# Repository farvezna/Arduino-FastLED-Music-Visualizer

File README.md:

# Arduino FastLED Music Visualizer
NOTE: I created my own PCB to hold an Arduino Nano to gain more practice with PCB layout and soldering through this cool project but all credits to code for RGB lighting are from Just Call Me Koko and the rest of the README below is of his works. The schematic used is essentially a replication of Sparkfun's spectrum shield mentioned below. My contributions are within the Nabid PCB folder.

<p align="center">
  
  <br>
  <a href="https://www.instagram.com/the.red.team4">Instagram</a>
 - <a href="https://www.youtube.com/channel/UCQdi3MDHHMm7u3cMkEY329Q">YouTube</a>
 - <a href="https://208.68.37.54">Website</a>
  <br>
  <br>
  <b>Like my content? Show your support by subscribing to my channel and following my page.</b>
</p>

# Table Of Constituents
- [Intro](#intro)
- [Setup](#setup)
  - [Video Tutorial](https://www.youtube.com/watch?v=Af74A0Tx-wA)
  - [Materials](#materials)
  - [Standalone Arduino UNO Setup](#standalone-arduino-uno-setup)
    - [Code](#code)
    - [Pins](#pins)
  - [Arduino UNO with Sparkfun Spectrum Shield Setup](#arduino-uno-with-sparkfun-spectrum-shield-setup)
    - [Code](#code)
    - [Pins](#pins)

## Intro
An Arduino based music visualizer using the FastLED library and a strip of individually addressable LEDs.  
Imagine this scenario. Does this not make you want to create your own music visualizer?

`> crawled inside of the neighbor's dog`  
`> dog walks inside of neighbor house`  
`> broke into neighbor house by being inside of dog`  
`> it is night now`  
`> brown cow`  
`> creep upstairs to find their mushroom farm`  
`> go into bed room`  
`> nothing`  
`> turn to leave`  
`> emergency yogurt falls out of pocket onto hardwood floor of bedroom`  
`> yogurt everywhere`  
`> wife gets up`  
`> slips on yogurt`  
`> impaled by mattress and is dead`  
`> yogurt murder`  
`> heinous Crims`  
`> power dump on dad's face so he doesn't feel as bad about his dead yogurt wife`  
`> poop yogurt and leave`  
`> poo and yogurt all over`  
`> in the air`  
`> zero gravity and poop`  

I can't find a guide worth a shit on YouTube or Github. I saw many videos showing a demo of a DIY music visualizer using these exact lights and an arduino. People seem to love to brag about how awesome their shit is but they won't show you how to make it. I have created this repo for anyone who faces the same challenge I did. I hope you find this useful and beneficial to your daily intake of fiber.

# Setup
So this is how to setup the most "dank" music visualizer ever.  
There will be two ways to set this puppy up. I prefer the second way, but that costs money.
There is a full video tutorial [here](https://www.youtube.com/watch?v=Af74A0Tx-wA)

## Materials
- [Arduino UNO](https://www.amazon.com/gp/product/B01N4LP86I/ref=oh_aui_detailpage_o06_s00?ie=UTF8&psc=1)
- [WS2812b Individually Addressable LEDs](https://www.amazon.com/gp/product/B01CDTEJBG/ref=oh_aui_detailpage_o09_s00?ie=UTF8&psc=1)
- [Sparkfun Spectrum Shield](https://www.amazon.com/gp/product/B00X0K30I6/ref=oh_aui_detailpage_o07_s00?ie=UTF8&psc=1) (second method)

## Standalone Arduino UNO Setup
### Code
  1. Open [this](https://github.com/the-red-team/Arduino-FastLED-Music-Visualizer/blob/master/music_visualizer.ino) code in your Arduino editor
  2. Line 13, adjust `NUM_LEDS` to the number of LEDs you plan to use
  3. Upload to your Arduino UNO
  
### Pins
  - 5v - Connect to Vcc on LED strip
  - GND - Connect to GND on LED strip
  - A0 - Connect to the other end of the 3.5mm jack connected to your music source
    - A0 must be pulled down with a resistor (shown in the picture below)
  - 6 - Connect to DATA on LED strip

## Arduino UNO with Sparkfun Spectrum Shield Setup
For this version of the music visualizer, you will need the [Sparkfun Spectrum Shield](https://www.amazon.com/gp/product/B00X0K30I6/ref=oh_aui_detailpage_o07_s00?ie=UTF8&psc=1)  
I prefer this version because it allows you to split the audio signal into 7 seperate channels (bass, mids, treb). This is important for anyone who wants their music visualizer to respond only to bass like mine.

### Code
  1. Open [this](https://github.com/the-red-team/Arduino-FastLED-Music-Visualizer/blob/master/music_visualizer_sparkfun_spectrum_shield.ino) code in your Arduino IDE
  2. Line 15, adjust `NUM_LEDS` to the number of LEDs you plan to use
  3. Install the FastLED library under "Manage Libraries"
  4. Upload to your Arduino UNO
  
### Pins
  - 5v - Connect to Vcc on LED strip
  - GND - Connect to GND on LED strip
  - 6 - Connect to DATA on LED strip

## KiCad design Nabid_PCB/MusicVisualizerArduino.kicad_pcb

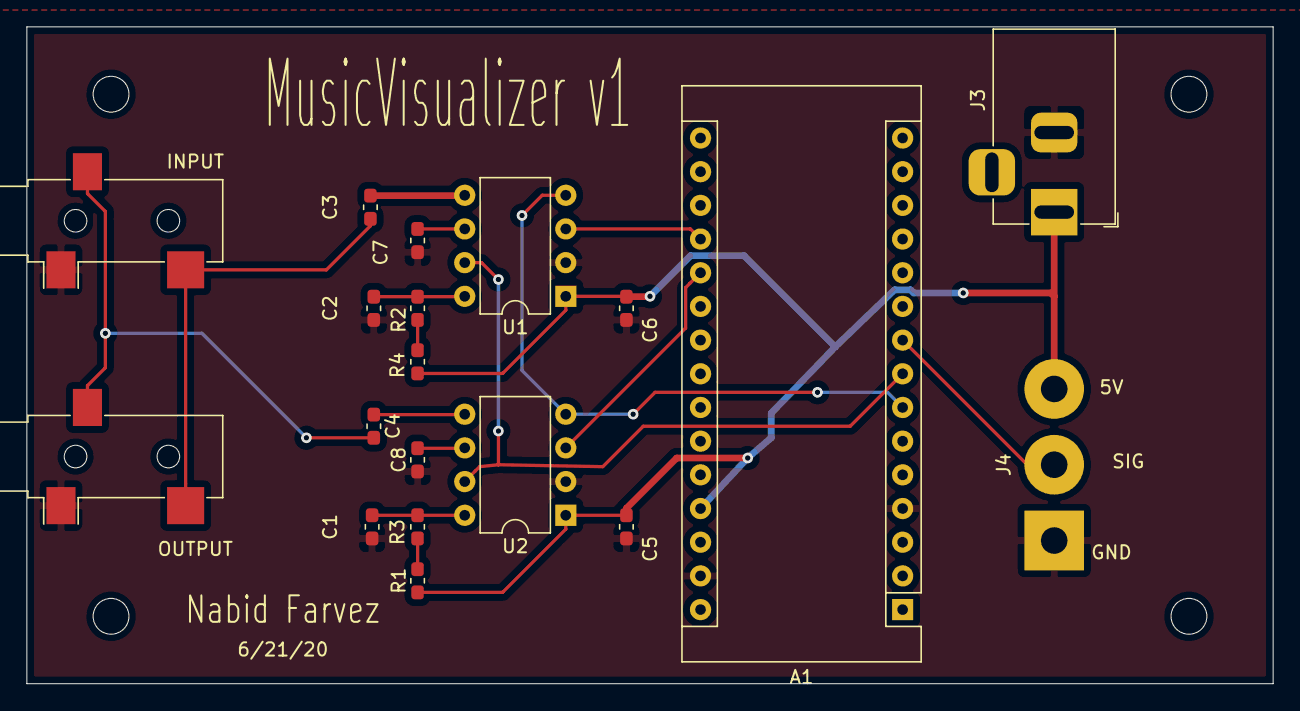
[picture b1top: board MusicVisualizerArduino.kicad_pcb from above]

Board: 2 copper layers, 94.0 x 49.5 mm, 19 parts (0 on the bottom side), 17 nets.

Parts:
A1: Arduino_Nano_v2.x; Arduino_Nano
C1, C2: 33 pF; C_0603_1608Metric_Pad1.05x0.95mm_HandSolder
C3, C4: 1 nF; C_0603_1608Metric_Pad1.05x0.95mm_HandSolder
C5, C6, C7, C8: 0.1 uF; C_0603_1608Metric_Pad1.05x0.95mm_HandSolder
INPUT: AudioJack3; Jack_3.5mm_CUI_SJ-3523-SMT_Horizontal
J3: Power_BarrelJack; BarrelJack_Horizontal
J4: RGB_STRIP; SolderWirePad_1x03_P5.715mm_Drill2mm
OUTPUT: AudioJack3; Jack_3.5mm_CUI_SJ-3523-SMT_Horizontal
R1, R2, R3, R4: 100K; R_0603_1608Metric_Pad1.05x0.95mm_HandSolder
U1, U2: MSGEQ7; DIP-8_W7.62mm

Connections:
+5V: A1.27, C5.1, C6.1, J3.1, J4.3, R1.1, R4.1, U1.1, U2.1
ANALOG0: A1.19, U1.3
ANALOG1: A1.20, U2.3
GND: A1.4, A1.29, C1.2, C2.2, C5.2, C6.2, C7.2, C8.1, INPUT.S, J3.2, J4.1, OUTPUT.S, U1.2, U2.2
LEFT: C3.2, INPUT.T, OUTPUT.T
unnamed: A1.9, J4.2
unnamed: C1.1, R3.2, U2.8
unnamed: C2.1, R2.2, U1.8
unnamed: C3.1, U1.5
unnamed: C4.1, U2.5
unnamed: C7.1, U1.6
unnamed: C8.2, U2.6
unnamed: R1.2, R3.1
unnamed: R2.1, R4.2
RESET: A1.8, U1.7, U2.7
RIGHT: C4.2, INPUT.R, OUTPUT.R
STROBE: A1.7, U1.4, U2.4

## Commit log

2020-06-22 added personal PCB design v1
2020-06-22 added pics of schematic and board render
2020-06-22 fixed board cut outline alignment
